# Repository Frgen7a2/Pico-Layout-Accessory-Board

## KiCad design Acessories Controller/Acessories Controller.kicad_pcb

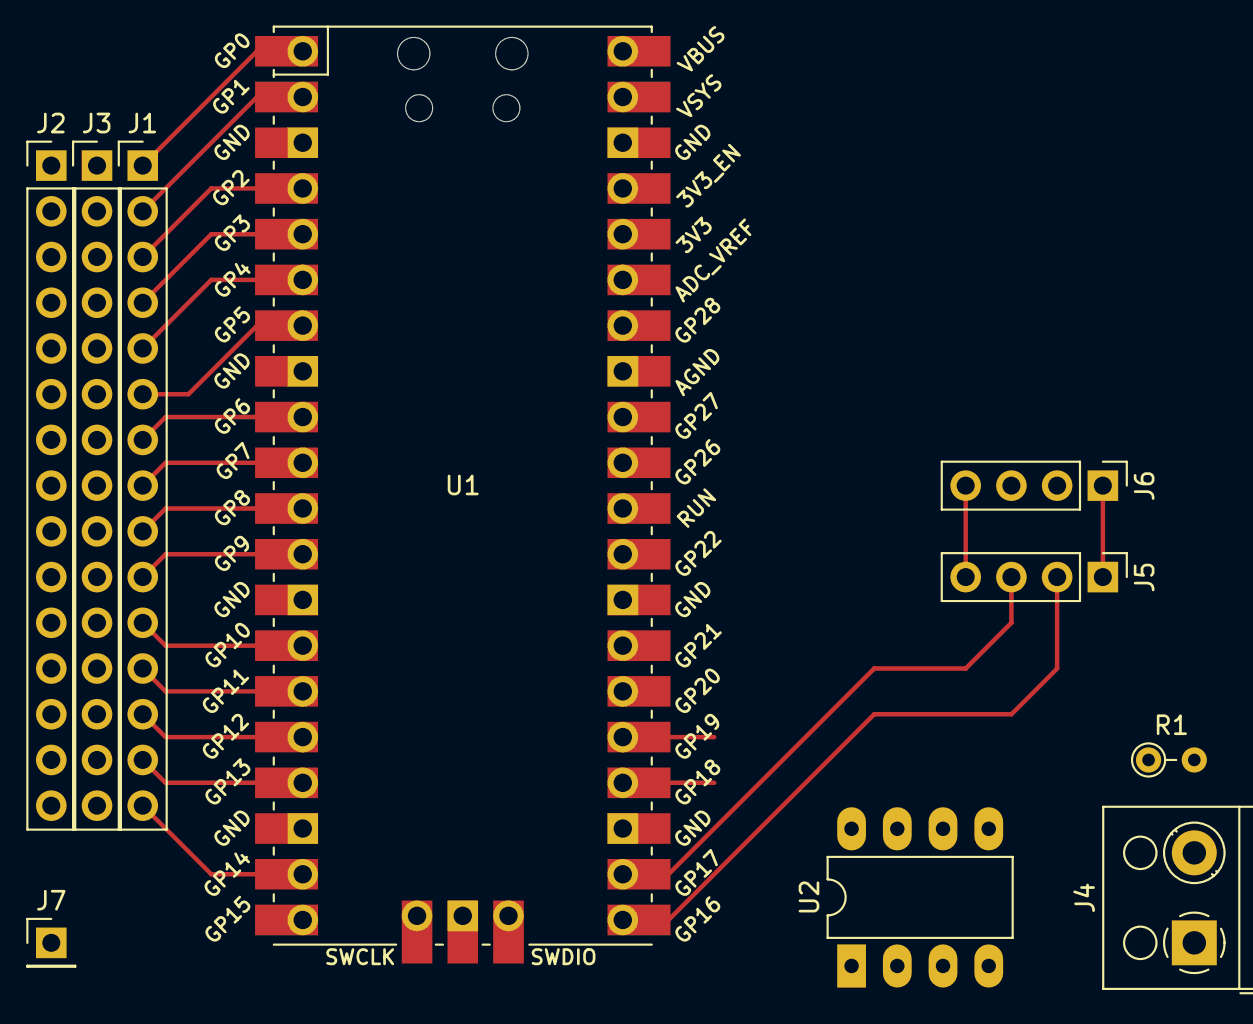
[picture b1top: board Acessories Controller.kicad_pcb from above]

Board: 2 copper layers, 10 parts (0 on the bottom side), 22 nets.

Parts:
J1, J2, J3: Conn_01x15_Pin; PinHeader_1x15_P2.54mm_Vertical
J4: Screw_Terminal_01x02; TerminalBlock_RND_205-00001_1x02_P5.00mm_Horizontal
J5, J6: Conn_01x04_Pin; PinHeader_1x04_P2.54mm_Vertical
J7: Conn_01x01; PinHeader_1x01_P2.54mm_Vertical
R1: 10; R_Axial_DIN0204_L3.6mm_D1.6mm_P2.54mm_Vertical
U1: Pico; RPi_Pico_SMD_TH
U2: LM386; DIP-8_W7.62mm_LongPads

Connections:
+5V: J2.1, J2.2, J2.3, J2.4, J2.5, J2.6, J2.7, J2.8, J2.9, J2.10, J2.11, J2.12, J2.13, J2.14, J2.15, J5.4, J6.4, U1.40 (VBUS), U2.6 (V+)
/I2C0SCL: J5.3, U1.22 (GPIO17)
/I2C0SDA: J5.2, U1.21 (GPIO16)
/SPI0SCK: J6.2, U1.24 (GPIO18)
/SPI0TX: J6.3, U1.25 (GPIO19)
GND: J3.1, J3.2, J3.3, J3.4, J3.5, J3.6, J3.7, J3.8, J3.9, J3.10, J3.11, J3.12, J3.13, J3.14, J3.15, J4.2, J5.1, J6.1, R1.2, U1.38 (GND), U2.2 (-), U2.4 (GND)
unnamed: J1.1, U1.1 (GPIO0)
unnamed: J1.2, U1.2 (GPIO1)
unnamed: J1.3, U1.4 (GPIO2)
unnamed: J1.4, U1.5 (GPIO3)
unnamed: J1.5, U1.6 (GPIO4)
unnamed: J1.6, U1.7 (GPIO5)
unnamed: J1.7, U1.9 (GPIO6)
unnamed: J1.8, U1.10 (GPIO7)
unnamed: J1.9, U1.11 (GPIO8)
unnamed: J1.10, U1.12 (GPIO9)
unnamed: J1.11, U1.14 (GPIO10)
unnamed: J1.12, U1.15 (GPIO11)
unnamed: J1.13, U1.16 (GPIO12)
unnamed: J1.14, U1.17 (GPIO13)
unnamed: J1.15, U1.19 (GPIO14)
unnamed: J7.1, U1.20 (GPIO15)

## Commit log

2023-05-16 Inital Push
